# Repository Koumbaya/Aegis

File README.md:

# Aegis
  
 The Aegis is a keyboard that uses the same layout as the crkbd by foostan : https://github.com/foostan/crkbd

 I wanted certain features like the solenoid so I made a quick PCB that's similar in layout to a crkbd but with only one pro-micro, you can make this PCB if you want a single PCB with underglow and a solenoid, or you can take the crkbd version of the case and slap both halves into this bad boy !
With the brass plate, it weight around 1Kg.
 
### CASE

If you're going for a metal 1,5mm switchplate (which you should, better sound yay !), you'll need to cut :
- One of every : Aegis_top1, Aegis_top2, Aegis_top3, Aegis_bottom in 3mm acrylic.
- Three times the Aegis_middle in 3mm acrylic
- One Aegis_switch_plate in 1,5mm metal of your choosing.

If you want to make everything in acrylic : just do as above minus one Aegis_middle.

You'll need 13 x M3 hex standoffs, >9mm if you have 3 "middle" part, >6 if you have only 2.
I've noticed that nylon standoffs are way larger than brass standoffs, so the dxf are designed for nylon standoff (brass ones will turn free) but can be modified.
You'll also need 13 x M3x5mm and 13 x M3x8mm screws.
The screws heads are hidden underneath the topmost plate, so you'll need something to hold it in place, probably some slim double-sided tape (will update once I've tested).
Note : be careful with the top1 and top2 cutouts, I broke mine when peeling the protective plastic sheet. (shoudn't have this problem on the crkbd version I think

### 3D printed case

This one is pretty much straightforward : print, put PCB inside, close.
There is a CRKBD version too.

 ### PCB
 
 The footprints for the diodes are either THT or SMD.
 
 The PCB uses SK6812mini-E for easier soldering, but the footprints are inverted compared to most keyboards :
 here the underglow LEDs are soldered from under the PCB (facing you when you solder them), instead of being soldered from the top. 

(soldered from under the PCB, led facing you. beware of the different orientations : the cut tab goes with the dot on the PCB)
 
 I did this because on my previous board some of the LEDs failed after that I had soldered all of the switches, meaning that to change them I had to desolder the switches.
 
 The center LED is soldered like a switch backlight led (from under the PCB, shining towards the top, through the PCB) because it's here to shine on the plate which have a logo cutout (a version without the logo is also available, in which case you'll probably want to just jump the trace for the led from IN to OUT).

(the cut tab goes on the top/right orientation, led facing back at you)

 For the solenoid you'll need 1 TIP120, 1 1N4001 diode, 1 1.1KOhms resistor and 1 5V solenoid.
Should look like this 
Note : in the v1.1, I've added a hole for the TIP120 because it's too big (by 0.3mm) to fit in the case. In mine I had to sand it down.

Note 2 : I couldn't get the solenoid to work :( with a pro micro I got a reboot, with the elite-c I discovered that the RAW port doesn't exist on it, so I took the VCC, with the same result. I've checked the schematics with some people and it should be good, so I'm putting in on the PCB anyway if someone want to have a crack at it(I've added 2 jumpers to get either VCC or RAW to the solenoid, if you have a pro micro, solder RAW, elite-c : solder VCC. Never both). If you find a solution let me know.

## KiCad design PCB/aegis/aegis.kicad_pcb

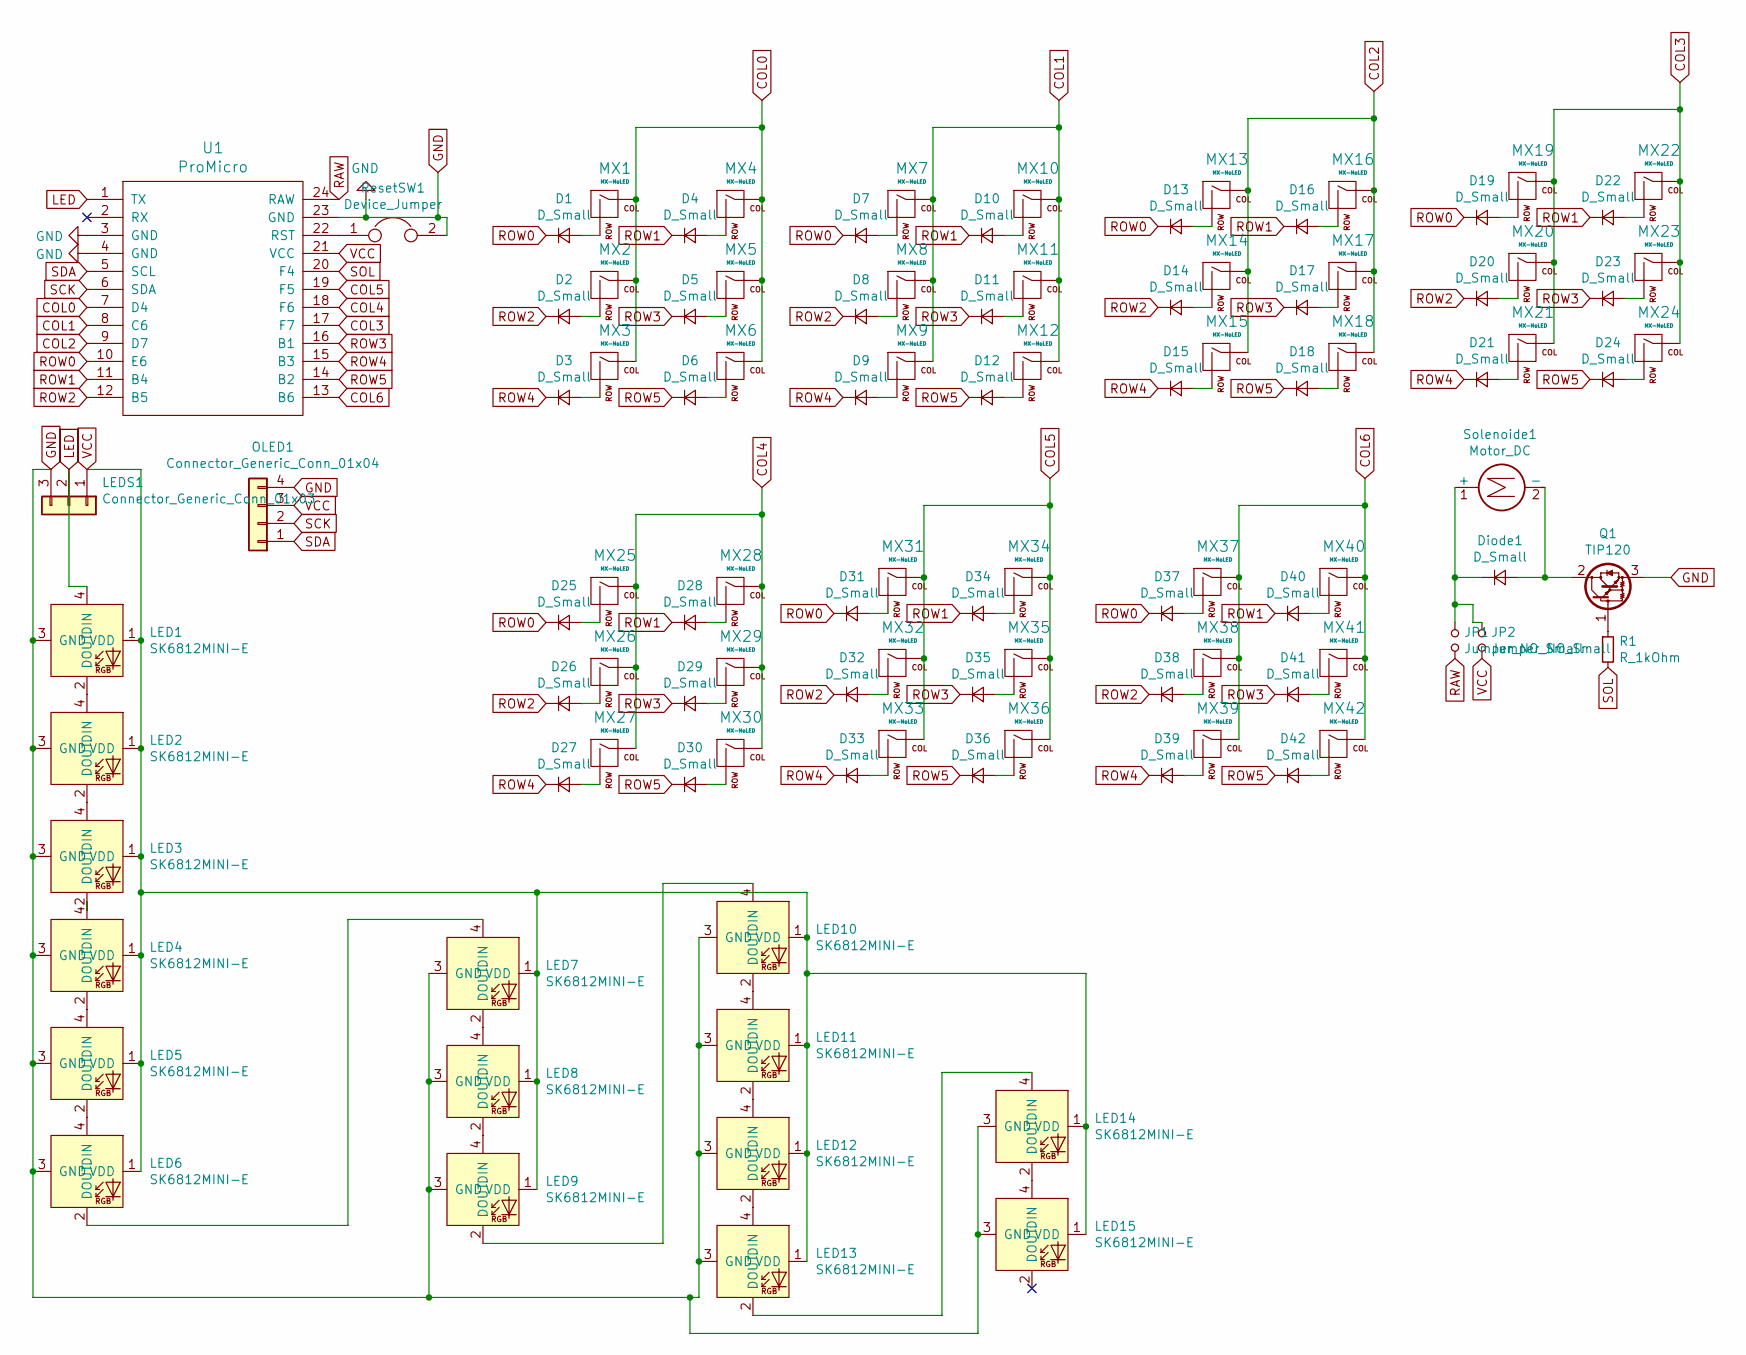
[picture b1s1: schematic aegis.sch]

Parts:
D1, D2, D3, D4, D5, D6, D7, D8, D9, D10, D11, D12, D13, D14, D15, D16, D17, D18, D19, D20, D21, D22, D23, D24, D25, D26, D27, D28, D29, D30, D31, D32, D33, D34, D35, D36, D37, D38, D39, D40, D41, D42: D_Small; D3_TH_SMD
Diode1: D_Small; D3_TH_SMD
JP1, JP2: Jumper_NO_Small; SolderJumper-2_P1.3mm_Open_Pad1.0x1.5mm
LED1, LED2, LED3, LED4, LED5, LED6, LED7, LED9, LED10, LED11, LED12, LED13, LED14, LED15: SK6812MINI-E; INV-YS-SK6812MINI-
LED8: SK6812MINI-E; YS-SK6812MINI-E
LEDS1: Connector_Generic_Conn_01x03; FanPinHeader_1x03_P2.54mm_Vertical
MX1, MX2, MX3, MX4, MX5, MX6, MX7, MX8, MX9, MX10, MX11, MX12, MX13, MX14, MX15, MX16, MX17, MX18, MX19, MX20, MX21, MX22, MX23, MX24, MX25, MX26, MX27, MX28, MX29, MX30, MX31, MX32, MX33, MX34, MX35, MX36, MX37, MX38, MX39, MX40, MX41, MX42: MX-NoLED; MXOnly-1U-NoLED
OLED1: Connector_Generic_Conn_01x04; FanPinHeader_1x04_P2.54mm_Vertical
Q1: TIP120; TO-220-3_Horizontal_TabDown
R1: R_1kOhm; R_Axial_DIN0204_L3.6mm_D1.6mm_P7.62mm_Horizontal
ResetSW1: Device_Jumper; ResetSW
Solenoide1: Motor_DC; ResetSW
U1: ProMicro

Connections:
COL0: MX1.1 (COL), MX2.1 (COL), MX3.1 (COL), MX4.1 (COL), MX5.1 (COL), MX6.1 (COL), U1.7 (D4)
COL1: MX7.1 (COL), MX8.1 (COL), MX9.1 (COL), MX10.1 (COL), MX11.1 (COL), MX12.1 (COL), U1.8 (C6)
COL2: MX13.1 (COL), MX14.1 (COL), MX15.1 (COL), MX16.1 (COL), MX17.1 (COL), MX18.1 (COL), U1.9 (D7)
COL3: MX19.1 (COL), MX20.1 (COL), MX21.1 (COL), MX22.1 (COL), MX23.1 (COL), MX24.1 (COL), U1.17 (F7)
COL4: MX25.1 (COL), MX26.1 (COL), MX27.1 (COL), MX28.1 (COL), MX29.1 (COL), MX30.1 (COL), U1.18 (F6)
COL5: MX31.1 (COL), MX32.1 (COL), MX33.1 (COL), MX34.1 (COL), MX35.1 (COL), MX36.1 (COL), U1.19 (F5)
COL6: MX37.1 (COL), MX38.1 (COL), MX39.1 (COL), MX40.1 (COL), MX41.1 (COL), MX42.1 (COL), U1.13 (B6)
GND: LED1.3 (GND), LED2.3 (GND), LED3.3 (GND), LED4.3 (GND), LED5.3 (GND), LED6.3 (GND), LED7.3 (GND), LED8.3 (GND), LED9.3 (GND), LED10.3 (GND), LED11.3 (GND), LED12.3 (GND), LED13.3 (GND), LED14.3 (GND), LED15.3 (GND), LEDS1.3, OLED1.4, Q1.3 (E), ResetSW1.2, U1.3 (GND), U1.4 (GND), U1.23 (GND); also elsewhere on the board
LED: LED1.4 (DIN), LEDS1.2, U1.1 (TX)
unnamed: D1.2 (A), MX1.2 (ROW)
unnamed: D2.2 (A), MX2.2 (ROW)
unnamed: D3.2 (A), MX3.2 (ROW)
unnamed: D4.2 (A), MX4.2 (ROW)
unnamed: D5.2 (A), MX5.2 (ROW)
unnamed: D6.2 (A), MX6.2 (ROW)
unnamed: D7.2 (A), MX7.2 (ROW)
unnamed: D8.2 (A), MX8.2 (ROW)
unnamed: D9.2 (A), MX9.2 (ROW)
unnamed: D10.2 (A), MX10.2 (ROW)
unnamed: D11.2 (A), MX11.2 (ROW)
unnamed: D12.2 (A), MX12.2 (ROW)
unnamed: D13.2 (A), MX13.2 (ROW)
unnamed: D14.2 (A), MX14.2 (ROW)
unnamed: D15.2 (A), MX15.2 (ROW)
unnamed: D16.2 (A), MX16.2 (ROW)
unnamed: D17.2 (A), MX17.2 (ROW)
unnamed: D18.2 (A), MX18.2 (ROW)
unnamed: D19.2 (A), MX19.2 (ROW)
unnamed: D20.2 (A), MX20.2 (ROW)
unnamed: D21.2 (A), MX21.2 (ROW)
unnamed: D22.2 (A), MX22.2 (ROW)
unnamed: D23.2 (A), MX23.2 (ROW)
unnamed: D24.2 (A), MX24.2 (ROW)
unnamed: D25.2 (A), MX25.2 (ROW)
unnamed: D26.2 (A), MX26.2 (ROW)
unnamed: D27.2 (A), MX27.2 (ROW)
unnamed: D28.2 (A), MX28.2 (ROW)
unnamed: D29.2 (A), MX29.2 (ROW)
unnamed: D30.2 (A), MX30.2 (ROW)
unnamed: D31.2 (A), MX31.2 (ROW)
unnamed: D32.2 (A), MX32.2 (ROW)
unnamed: D33.2 (A), MX33.2 (ROW)
unnamed: D34.2 (A), MX34.2 (ROW)
unnamed: D35.2 (A), MX35.2 (ROW)
unnamed: D36.2 (A), MX36.2 (ROW)
unnamed: D37.2 (A), MX37.2 (ROW)
unnamed: D38.2 (A), MX38.2 (ROW)
unnamed: D39.2 (A), MX39.2 (ROW)
unnamed: D40.2 (A), MX40.2 (ROW)
unnamed: D41.2 (A), MX41.2 (ROW)
unnamed: D42.2 (A), MX42.2 (ROW)
unnamed 51: Diode1.1 (K), JP1.1, JP2.1, Solenoide1.1 (+); also elsewhere on the board
unnamed: Diode1.2 (A), Q1.2 (C), Solenoide1.2 (-)
unnamed: LED1.2 (DOUT), LED2.4 (DIN)
unnamed: LED2.2 (DOUT), LED3.4 (DIN)
unnamed: LED3.2 (DOUT), LED4.4 (DIN)
unnamed: LED4.2 (DOUT), LED5.4 (DIN)
unnamed: LED5.2 (DOUT), LED6.4 (DIN)
unnamed: LED6.2 (DOUT), LED7.4 (DIN)
unnamed: LED7.2 (DOUT), LED8.4 (DIN)
unnamed: LED8.2 (DOUT), LED9.4 (DIN)
unnamed: LED10.2 (DOUT), LED11.4 (DIN)
unnamed: LED9.2 (DOUT), LED10.4 (DIN)
unnamed: LED11.2 (DOUT), LED12.4 (DIN)
unnamed: LED12.2 (DOUT), LED13.4 (DIN)
unnamed: LED13.2 (DOUT), LED14.4 (DIN)
unnamed: LED14.2 (DOUT), LED15.4 (DIN)
unnamed: Q1.1 (B), R1.1
unnamed: ResetSW1.1, U1.22 (RST)
RAW: JP1.2, U1.24 (RAW); also elsewhere on the board
ROW0: D1.1 (K), D7.1 (K), D13.1 (K), D19.1 (K), D25.1 (K), D31.1 (K), D37.1 (K), U1.10 (E6)
ROW1: D4.1 (K), D10.1 (K), D16.1 (K), D22.1 (K), D28.1 (K), D34.1 (K), D40.1 (K), U1.11 (B4)
ROW2: D2.1 (K), D8.1 (K), D14.1 (K), D20.1 (K), D26.1 (K), D32.1 (K), D38.1 (K), U1.12 (B5)
ROW3: D5.1 (K), D11.1 (K), D17.1 (K), D23.1 (K), D29.1 (K), D35.1 (K), D41.1 (K), U1.16 (B1)
ROW4: D3.1 (K), D9.1 (K), D15.1 (K), D21.1 (K), D27.1 (K), D33.1 (K), D39.1 (K), U1.15 (B3)
ROW5: D6.1 (K), D12.1 (K), D18.1 (K), D24.1 (K), D30.1 (K), D36.1 (K), D42.1 (K), U1.14 (B2)
SCK: OLED1.2, U1.6 (SDA); also elsewhere on the board
SDA: OLED1.1, U1.5 (SCL); also elsewhere on the board
SOL: R1.2, U1.20 (F4)
VCC: JP2.2, LED1.1 (VDD), LED2.1 (VDD), LED3.1 (VDD), LED4.1 (VDD), LED5.1 (VDD), LED6.1 (VDD), LED7.1 (VDD), LED8.1 (VDD), LED9.1 (VDD), LED10.1 (VDD), LED11.1 (VDD), LED12.1 (VDD), LED13.1 (VDD), LED14.1 (VDD), LED15.1 (VDD), LEDS1.1, OLED1.3, U1.21 (VCC); also elsewhere on the board

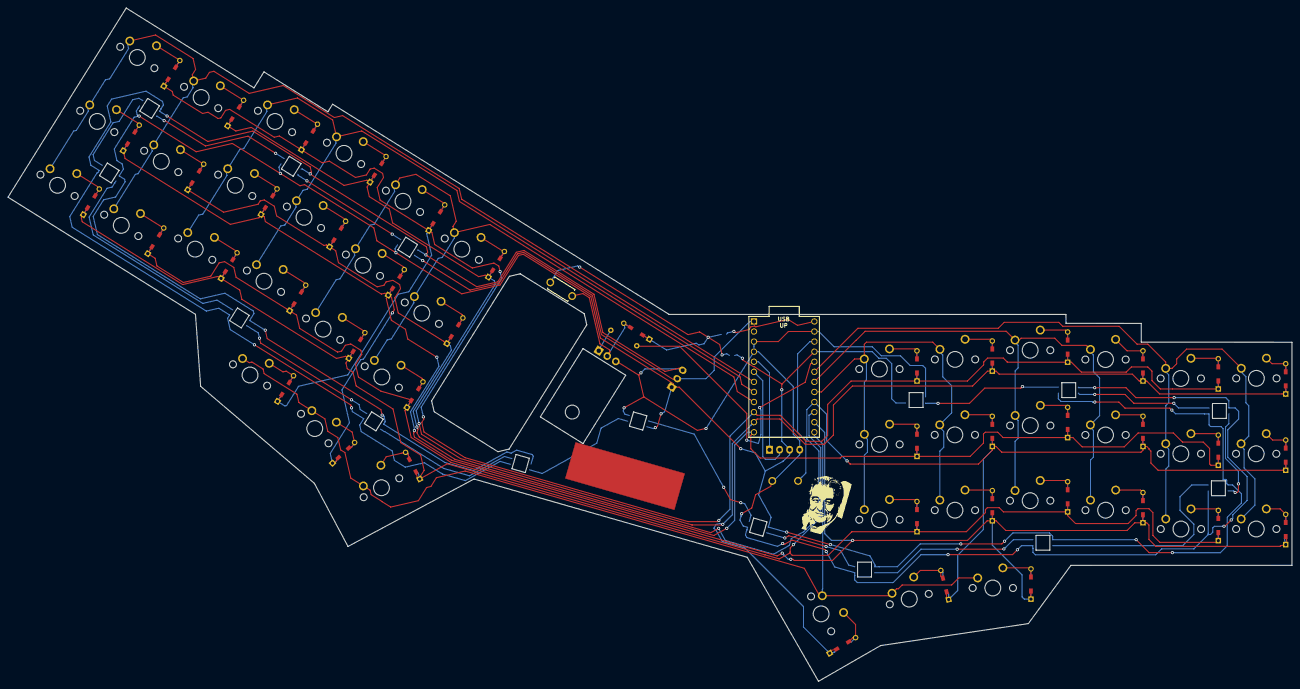
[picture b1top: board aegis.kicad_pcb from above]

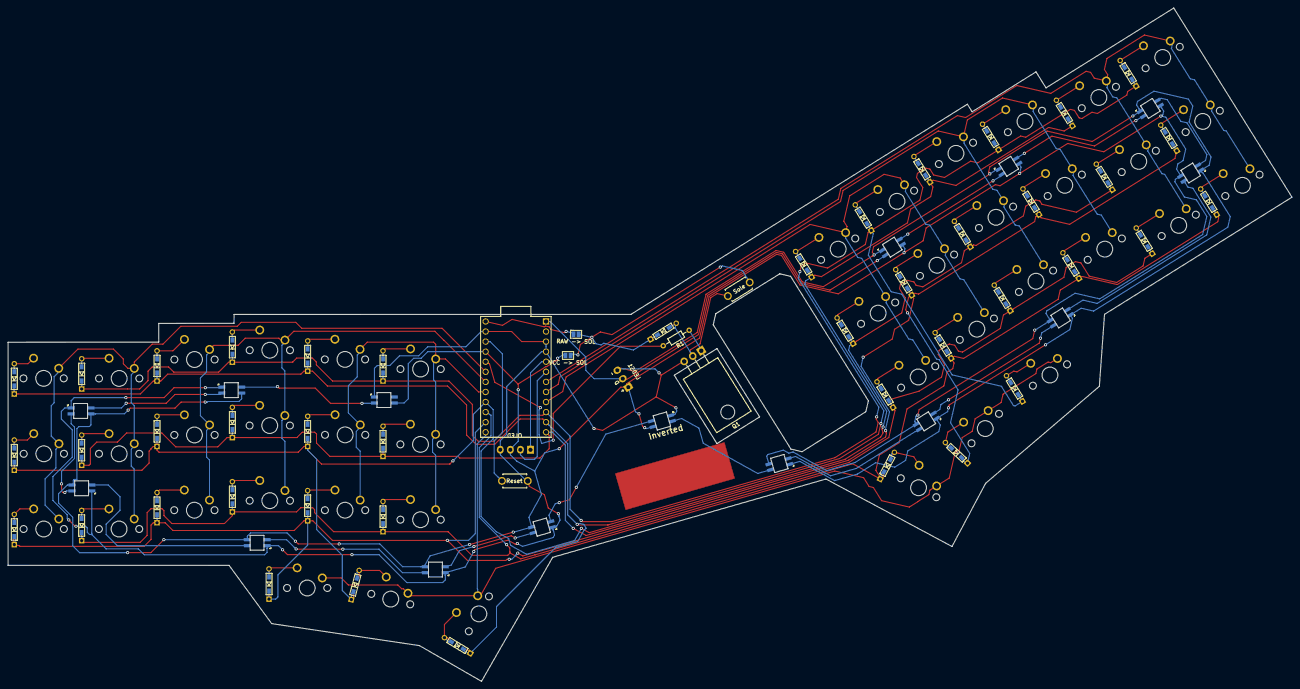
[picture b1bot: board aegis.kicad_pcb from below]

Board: 2 copper layers, 323.8 x 169.8 mm, 109 parts (5 on the bottom side), 80 nets.

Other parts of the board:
OLED: Connector_Generic_Conn_01x04; FanPinHeader_1x04_P2.54mm_Vertical
RAW -> SOL: Jumper_NO_Small; SolderJumper-2_P1.3mm_Open_Pad1.0x1.5mm
VCC -> SOL: Jumper_NO_Small; SolderJumper-2_P1.3mm_Open_Pad1.0x1.5mm

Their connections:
GND: OLED.4; also elsewhere on the board
unnamed 51: RAW -> SOL.1, VCC -> SOL.1; also elsewhere on the board
RAW: RAW -> SOL.2; also elsewhere on the board
SCK: OLED.2; also elsewhere on the board
SDA: OLED.1; also elsewhere on the board
VCC: OLED.3, VCC -> SOL.2; also elsewhere on the board

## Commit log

2020-10-24 save
2020-10-25 moved files
2020-10-31 add crkbd version
2020-10-31 erased a file by mistake
2020-11-01 change colors
2020-11-08 add pics
2020-11-11 add pic
2020-11-11 add qmk files
2021-03-12 add 3d printed case
